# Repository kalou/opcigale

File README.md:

# Opcigale
This is an electronic thing that chirps like a cricket, when the environment is quiet.

I'm learning electronics with this - so don't take anything below for granted.

I hope this can be useful to learn. Feel free to send improvements.

## Spec
- After a long enough silence, it starts singing.
- Whenever a noise occurs, it stops singing.
- It should react to lower frequencies (<500hz) and have a relatively high pitched song, so that it doesn't stop for its own or similar cricket sounds.
- An LED blinks when it detects a sound.
- A few knobs allow to tune sensitivity, cricket song, etc.

## Todo
- inhibit sound signal when it turns on, to ignore noise in circuit
- add a photoresistor, to also require low luminosity to start singing

## Caveats
The circuit is sensitive to noise, e.g. when the song circuitry turns on.

## Design

### Microphone
An electret microphone is powered to its operating voltage of ~4.5v (specs vary).
C4 is decoupling the next stage from the DC signal. With an impedance of ~300 ohms at 500hz,
C5 helps throw higher frequencies away.

### Amplification
The first half of a dual op-amp is configured to amplify the smallest ~1mv spikes to a few
hundred millivolts. This is enough to detect a voice from a couple meters.

R6/R7 provide a reference voltage of 4.5v, and we power the op amp with +9v, 0v.
C6 and C10 attempt to reduce noise in the power line.

### Detection
There's a voltage divider provided by RV1 which will bias the transistor Q4
close to a base-emitter voltage of .6v - C7 removes DC (we're half-way at 4.5v)
from the amplifier stage and adds the AC signal to the base.

When Q4 turns on, led blinks (C8 buffers some current to reduce noise in circuit) and
the output of this stage (which is the base of Q5) pulls low.

By tuning RV1 we can make it more or less sensitive. I guess doing this tuning here
is not the most efficient way, as current leaks to led when we increase sensitivity,
producing a glow, but total consumption is still pretty low in the couple of mA range.

### Timer
C9 slowly charges through R16. Vary R or C to configure delay - it will reach 4.5v 
at 0.7 * RC - this is detected by the voltage comparator built with the second half
of the op-amp in U4B, borrowing the amplifier's voltage divider as its reference.

Works with LM358, but may need some biasing for op amps that don't want to work
too close to the rail voltages (0v here)?

With the debugging setup shown here (10uF and 1Mohm) this takes around 7 seconds.

Whenever the previous stage detects a noise, Q5 base is grounded, leading to C9
discharging into R17 via this transistor, which resets the timer.

When the charge reaches 4.5v, pin 7 of U4 turns high, which turns Q6 on, powering
on the full song stage below. There's a bit of electrical noise when this happens
and there should be a R limiting current going to that circuit.

There's no hysteresis on charge/discharge of C9 so we can have some startup
hesitations, especially when the C9 is set to charge very slow, and microphone
sensitivity is set high. Eventually as C9 charges we have more budget and the
next stage can start.

### Song
We use inverters to build three oscillators.

The .1uF/48k RC at U1C produces a 5khz high pitch sound. U1A and U1B provide two
slower oscillations, to manipulate the envelope.

## AQ
### Why opcigale
I wanted to have fun with electronics. I had an electret microphone, and no idea how it worked.
Cigale means cicada in french. But I guess I meant grillon, which is a cricket. I actually ignore
if cicadas shut up when you walk nearby.

First version was using transistors, hence this version is called "opcigale".

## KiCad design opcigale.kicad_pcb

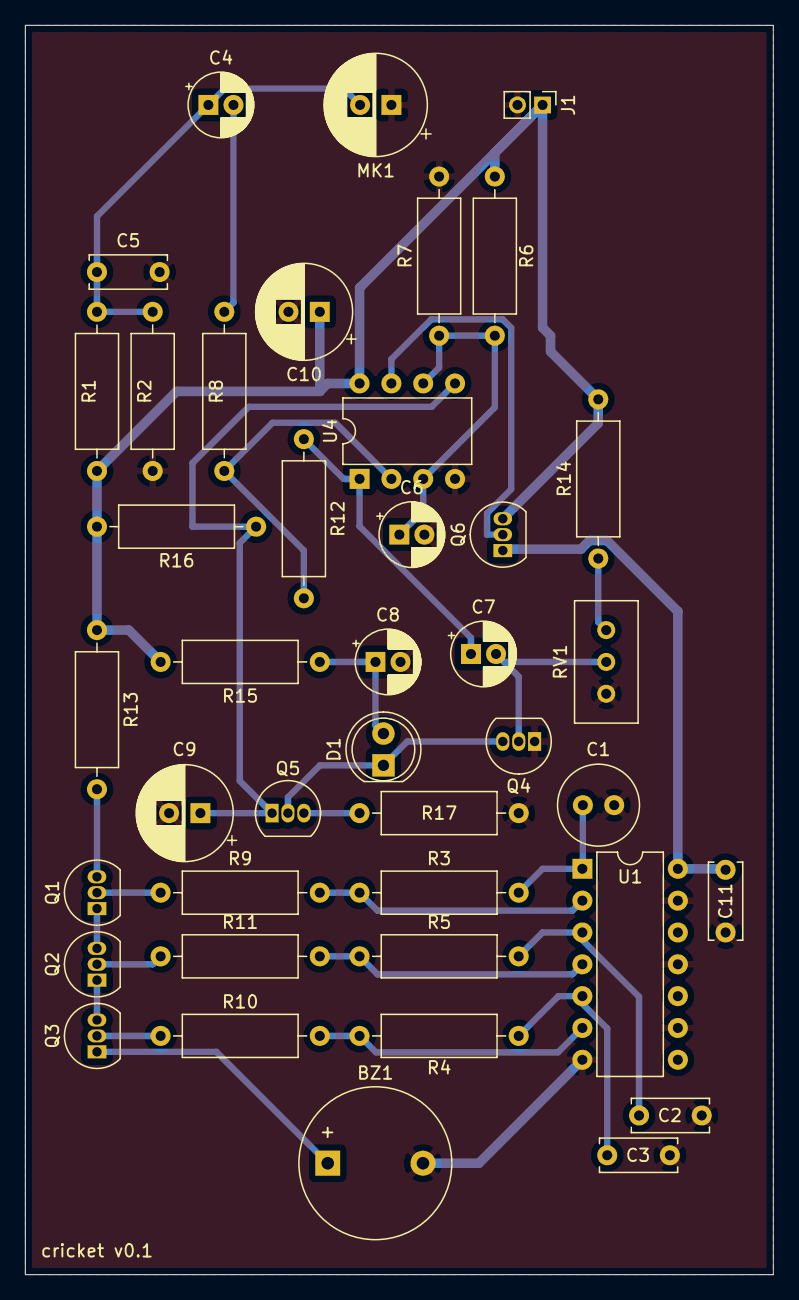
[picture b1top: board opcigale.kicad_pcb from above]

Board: 2 copper layers, 59.7 x 99.7 mm, 41 parts (0 on the bottom side), 28 nets.

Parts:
BZ1: Buzzer; Buzzer_12x9.5RM7.6
C1: 10uF; C_Radial_D6.3mm_H11.0mm_P2.50mm
C2: 2.2uF; C_Disc_D6.0mm_W2.5mm_P5.00mm
C3: 0.01uF; C_Disc_D6.0mm_W2.5mm_P5.00mm
C4: 10uF; CP_Radial_D5.0mm_P2.00mm
C5: 1uF; C_Disc_D6.0mm_W2.5mm_P5.00mm
C6, C7, C8: 1uF; CP_Radial_D5.0mm_P2.00mm
C9: Delay (10uF= 5s); CP_Radial_D7.5mm_P2.50mm
C10: 100uF; CP_Radial_D7.5mm_P2.50mm
C11: 0.1uF; C_Disc_D6.0mm_W2.5mm_P5.00mm
D1: LED; LED_D5.0mm
J1: bat; PinHeader_1x02_P2.00mm_Vertical
MK1: Microphone_Condenser; CP_Radial_D8.0mm_P2.50mm
Q1, Q2, Q3, Q4, Q6: 2N3904; TO-92_Inline
Q5: 2N3906; TO-92_Inline
R1, R2, R6, R7: 10k; R_Axial_DIN0309_L9.0mm_D3.2mm_P12.70mm_Horizontal
R3, R4, R5: 48k; R_Axial_DIN0309_L9.0mm_D3.2mm_P12.70mm_Horizontal
R8: 330; R_Axial_DIN0309_L9.0mm_D3.2mm_P12.70mm_Horizontal
R9, R10, R11, R14: 20k; R_Axial_DIN0309_L9.0mm_D3.2mm_P12.70mm_Horizontal
R12: 600k; R_Axial_DIN0309_L9.0mm_D3.2mm_P12.70mm_Horizontal
R13: 1k; R_Axial_DIN0309_L9.0mm_D3.2mm_P12.70mm_Horizontal
R15: 5k; R_Axial_DIN0309_L9.0mm_D3.2mm_P12.70mm_Horizontal
R16: 1M; R_Axial_DIN0309_L9.0mm_D3.2mm_P12.70mm_Horizontal
R17: 100; R_Axial_DIN0309_L9.0mm_D3.2mm_P12.70mm_Horizontal
RV1: R_POT 2k W202; Potentiometer_Bourns_3296W_Vertical
U1: 40106; DIP-14_W7.62mm
U4: LM358; DIP-8_W7.62mm

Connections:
+9V: C10.1, J1.1, Q6.3, R1.1, R6.2, R13.1, R14.2, R15.2, R16.2, U4.8
GND: BZ1.2, C1.1, C2.1, C3.1, C5.2, C6.2, C8.2, C9.2, C10.2, C11.1, J1.2, MK1.1, Q4.1, R2.2, R7.2, R17.1, RV1.3, U1.7, U1.9, U1.11, U1.13, U4.4
unnamed: BZ1.1, Q3.1
unnamed: C1.2, R3.2, U1.1
unnamed: C2.2, R5.2, U1.3
unnamed: C3.2, R4.2, U1.5
unnamed: C4.1, C5.1, MK1.2, R1.2, R2.1
unnamed: C4.2, R8.2
unnamed: C6.1, R6.1, R7.1, U4.3, U4.6
unnamed: C7.1, R12.1, U4.1
unnamed: C7.2, Q4.2, RV1.2
unnamed: C8.1, D1.2, R15.1
unnamed: C9.1, Q5.1, R16.1, U4.5
unnamed: D1.1, Q4.3, Q5.2
unnamed: Q1.1, Q2.3
unnamed: Q1.2, R9.1
unnamed: Q1.3, R13.2
unnamed: Q2.1, Q3.3
unnamed: Q2.2, R11.1
unnamed: Q3.2, R10.1
unnamed: Q5.3, R17.2
unnamed: Q6.2, U4.7
unnamed: R3.1, R9.2, U1.2
unnamed: R4.1, R10.2, U1.6
unnamed: R5.1, R11.2, U1.4
unnamed: R8.1, R12.2, U4.2
unnamed: R14.1, RV1.1
SND: C11.2, Q6.1, U1.14

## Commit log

2022-01-08 initial
2022-01-14 Fix schema/PCB errors, add README
2022-01-16 Add opcigale-F_Fab.pdf for assembling ref
    Also fix resistor values for oscillators
